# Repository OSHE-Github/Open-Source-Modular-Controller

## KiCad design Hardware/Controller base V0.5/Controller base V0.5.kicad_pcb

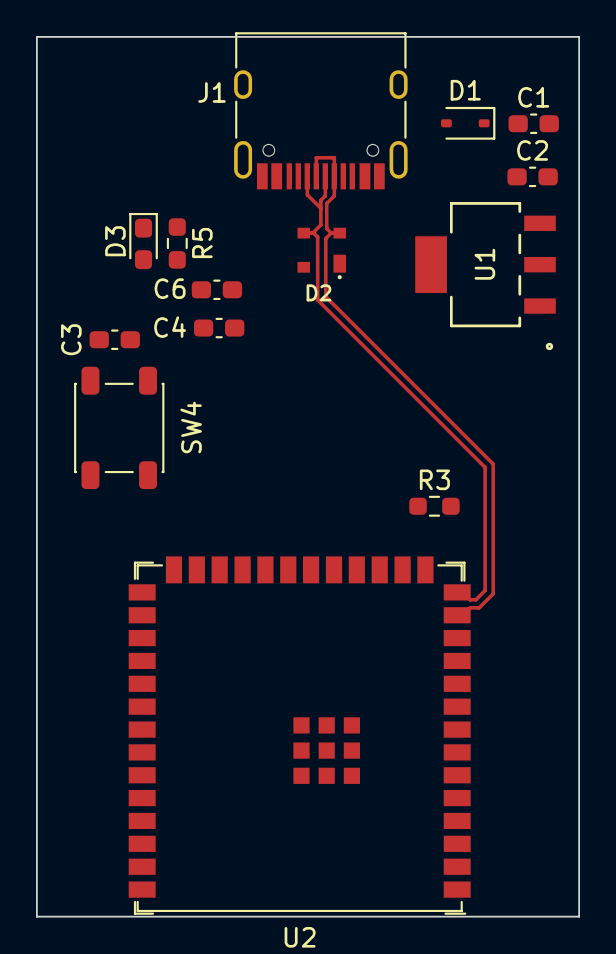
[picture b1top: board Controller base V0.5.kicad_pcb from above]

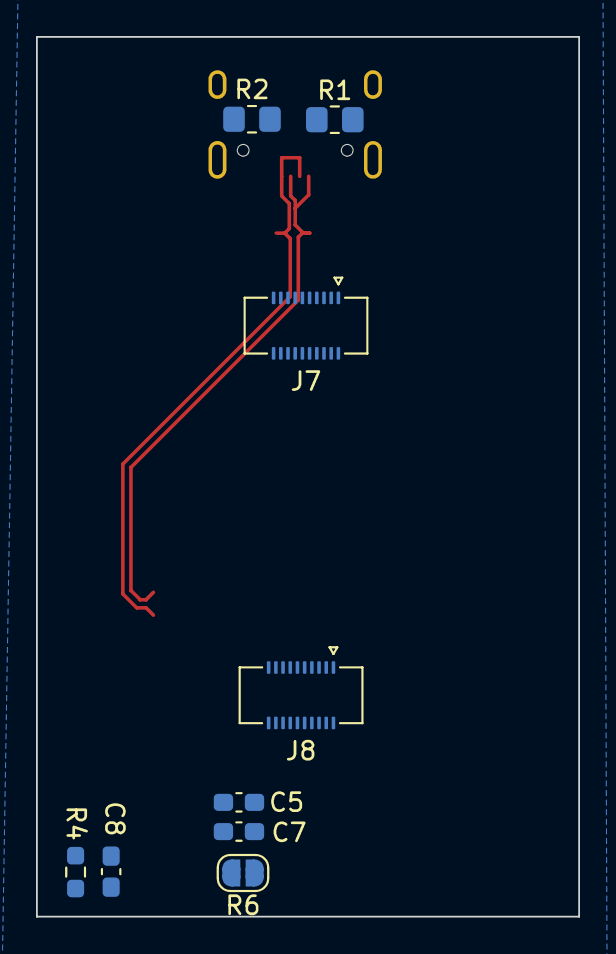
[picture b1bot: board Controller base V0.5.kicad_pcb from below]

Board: 2 copper layers, 30.1 x 48.9 mm, 23 parts (9 on the bottom side), 41 nets.

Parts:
C1, C5, C6: 10uF; C_0603_1608Metric_Pad1.08x0.95mm_HandSolder
C2, C3, C4, C7: 0.1uF; C_0603_1608Metric_Pad1.08x0.95mm_HandSolder
C8: 1uF; C_0603_1608Metric_Pad1.08x0.95mm_HandSolder
D1: 1N5819WS; D_SOD-323
D2: PRTR5V0U2X_215
D3: LED; LED_0603_1608Metric_Pad1.05x0.95mm_HandSolder
J1: USB_C_Receptacle_USB2.0_16P; USB_C_Receptacle_HRO_TYPE-C-31-M-12
J7, J8: Conn_02x10_Counter_Clockwise; Hirose_DF40C-20DS-0.4V_2x10_P0.4mm
R1, R2: 5.1K; R_0805_2012Metric_Pad1.20x1.40mm_HandSolder
R3, R5: 1K; R_0603_1608Metric_Pad0.98x0.95mm_HandSolder
R4: 10K; R_0603_1608Metric_Pad0.98x0.95mm_HandSolder
R6: 0; SolderJumper-2_P1.3mm_Open_RoundedPad1.0x1.5mm
SW4: SW_Push; SW_SPST_PTS647_Sx38
U1: AZ1117CH-3.3TRG1; SOT-223_DIO
U2: ESP32-S3-WROOM-1U-N4; ESP32-S3-WROOM-1U

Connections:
/CC1: J1.A5 (CC1), R2.2
/CC2: J1.B5 (CC2), R1.2
/CHIP_PU: C8.1, R4.1, U2.3 (EN)
D+: D2.3, J1.A6 (D+), J1.B6 (D+), U2.14 (USB_D+)
D-: D2.2, J1.A7 (D-), J1.B7 (D-), U2.13 (USB_D-)
ESP_3.3V: R4.2, R6.2, U2.2 (3V3)
GND: C1.2, C2.2, C3.1, C4.2, C5.2, C6.2, C7.2, C8.2, D2.1, D3.1 (K), J1.A1 (GND), J1.A12 (GND), J1.B1 (GND), J1.B12 (GND), J1.S1 (SHIELD), J7.11, J7.13, J7.15, J8.15, J8.17, J8.19, R1.1, R2.1, SW4.1, U1.1 (GND), U2.1 (GND), U2.40 (GND), U2.41 (GND)
GPIO0: C3.2, SW4.2, U2.27 (IO0)
GPIO1: J8.12, U2.39 (IO1)
GPIO2: J8.10, U2.38 (IO2)
GPIO3: J7.16, R3.1, U2.15 (IO3)
GPIO4: J8.14, U2.4 (IO4)
GPIO5: J8.16, U2.5 (IO5)
GPIO6: J8.18, U2.6 (IO6)
GPIO7: J8.20, U2.7 (IO7)
GPIO8: J7.18, U2.12 (IO8)
GPIO9: J7.14, U2.17 (IO9)
GPIO10: J7.12, U2.18 (IO10)
GPIO11: J7.10, U2.19 (IO11)
GPIO12: J7.8, U2.20 (IO12)
GPIO13: J7.6, U2.21 (IO13)
GPIO14: J7.4, U2.22 (IO14)
GPIO15: J8.9, U2.8 (IO15)
GPIO16: J8.11, U2.9 (IO16)
GPIO17: J8.13, U2.10 (IO17)
GPIO18: J7.20, U2.11 (IO18)
GPIO21: J7.2, U2.23 (IO21)
GPIO35: J8.1, U2.28 (IO35)
GPIO36: J8.3, U2.29 (IO36)
GPIO37: J8.5, U2.30 (IO37)
GPIO38: J8.7, U2.31 (IO38)
GPIO41: J8.2, U2.34 (IO41)
GPIO42: J8.4, U2.35 (IO42)
GPIO47: J7.3, U2.24 (IO47)
GPIO48: J7.1, U2.25 (IO48)
unnamed: D3.2 (A), R5.2
RXD0: J8.6, U2.36 (RXD0)
TXD0: J8.8, U2.37 (TXD0)
VBUS: D1.2 (A), D2.4, J1.A4 (VBUS), J1.A9 (VBUS), J1.B4 (VBUS), J1.B9 (VBUS)
VCC_3V3: C4.1, C5.1, C6.1, C7.1, J7.5, J7.7, J7.9, R3.2, R5.1, R6.1, U1.2 (OUTPUT)
VCC_5V: C1.1, C2.1, D1.1 (K), J7.17, J7.19, U1.3 (INPUT)

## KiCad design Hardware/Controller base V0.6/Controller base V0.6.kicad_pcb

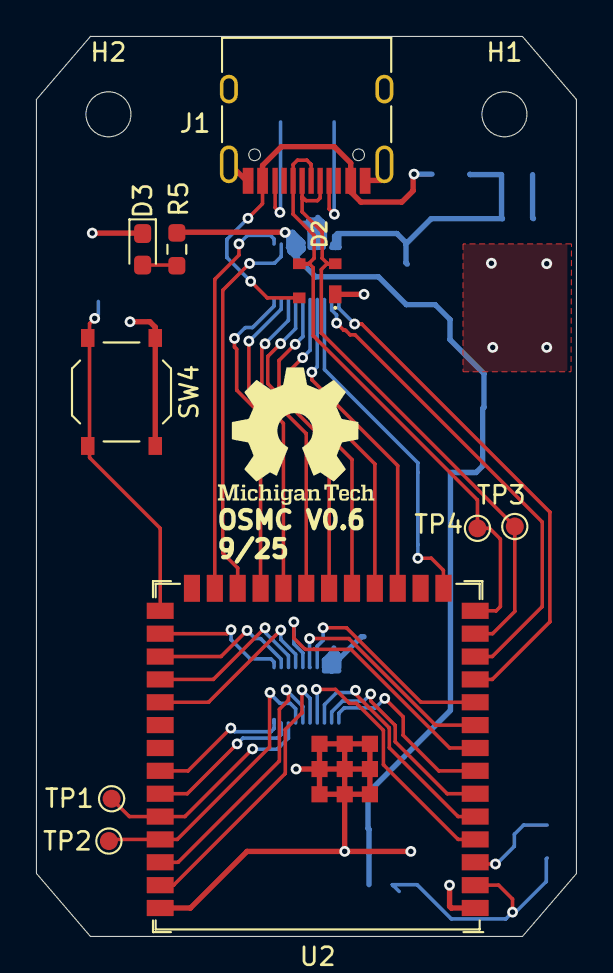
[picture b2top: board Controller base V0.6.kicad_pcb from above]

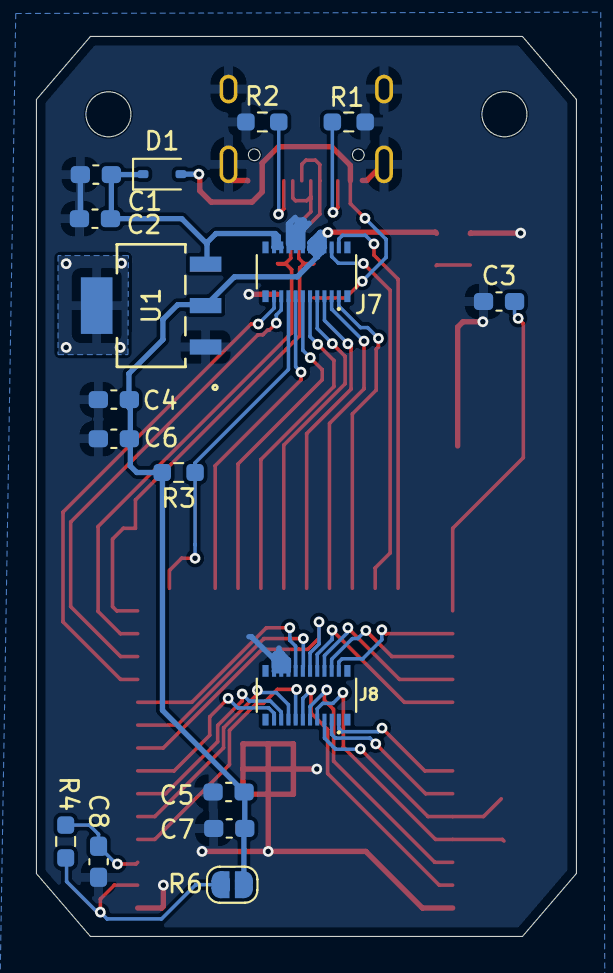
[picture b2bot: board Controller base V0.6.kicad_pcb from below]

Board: 2 copper layers, 30.0 x 50.0 mm, 29 parts (17 on the bottom side), 41 nets.

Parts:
C1, C5, C6: 10uF; C_0603_1608Metric_Pad1.08x0.95mm_HandSolder
C2, C3, C4, C7: 0.1uF; C_0603_1608Metric_Pad1.08x0.95mm_HandSolder
C8: 1uF; C_0603_1608Metric_Pad1.08x0.95mm_HandSolder
D1: 1N5819WS; D_SOD-323
D2: PRTR5V0U2X_215
D3: LED; LED_0603_1608Metric_Pad1.05x0.95mm_HandSolder
H1, H2: MountingHole; MountingHole_2.5mm
J1: USB_C_Receptacle_USB2.0_16P; USB_C_Receptacle_HRO_TYPE-C-31-M-12
J7, J8: Conn_02x10_Counter_Clockwise; HRS_DF40C-20DP-0.4V_51_
R1, R2: 5.1K; R_0603_1608Metric_Pad0.98x0.95mm_HandSolder
R3, R5: 1K; R_0603_1608Metric_Pad0.98x0.95mm_HandSolder
R4: 10K; R_0603_1608Metric_Pad0.98x0.95mm_HandSolder
R6: 0; SolderJumper-2_P1.3mm_Open_RoundedPad1.0x1.5mm
SW4: SW_Push; SW_Push_1P1T_XKB_TS-1187A
TP1, TP2, TP3, TP4: TestPoint; TestPoint_Pad_D1.0mm
U1: AZ1117CH-3.3TRG1; SOT-223_DIO
U2: ESP32-S3-WROOM-1U-N4; ESP32-S3-WROOM-1U

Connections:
/CC1: J1.A5 (CC1), R2.2
/CC2: J1.B5 (CC2), R1.2
/CHIP_PU: C8.1, R4.1, U2.3 (EN)
D+: D2.3, J1.A6 (D+), J1.B6 (D+), TP4.1, U2.14 (USB_D+)
D-: D2.2, J1.A7 (D-), J1.B7 (D-), TP3.1, U2.13 (USB_D-)
ESP_3.3V: R4.2, R6.2, U2.2 (3V3)
GND: C1.2, C2.2, C3.1, C4.2, C5.2, C6.2, C7.2, C8.2, D2.1, D3.1 (K), J1.A1 (GND), J1.A12 (GND), J1.B1 (GND), J1.B12 (GND), J1.S1 (SHIELD), J7.12, J7.14, J7.16, J8.16, J8.18, J8.20, R1.1, R2.1, SW4.1, U1.1 (GND), U2.1 (GND), U2.40 (GND), U2.41 (GND)
GPIO0: C3.2, SW4.2, U2.27 (IO0)
GPIO1: J8.11, U2.39 (IO1)
GPIO2: J8.9, U2.38 (IO2)
GPIO3: J7.15, R3.1, U2.15 (IO3)
GPIO4: J8.13, U2.4 (IO4)
GPIO5: J8.15, U2.5 (IO5)
GPIO6: J8.17, U2.6 (IO6)
GPIO7: J8.19, U2.7 (IO7)
GPIO8: J7.17, U2.12 (IO8)
GPIO9: J7.13, U2.17 (IO9)
GPIO10: J7.11, U2.18 (IO10)
GPIO11: J7.9, U2.19 (IO11)
GPIO12: J7.7, U2.20 (IO12)
GPIO13: J7.5, U2.21 (IO13)
GPIO14: J7.3, U2.22 (IO14)
GPIO15: J8.10, U2.8 (IO15)
GPIO16: J8.12, U2.9 (IO16)
GPIO17: J8.14, U2.10 (IO17)
GPIO18: J7.19, U2.11 (IO18)
GPIO21: J7.1, U2.23 (IO21)
GPIO35: J8.2, U2.28 (IO35)
GPIO36: J8.4, U2.29 (IO36)
GPIO37: J8.6, U2.30 (IO37)
GPIO38: J8.8, U2.31 (IO38)
GPIO41: J8.1, U2.34 (IO41)
GPIO42: J8.3, U2.35 (IO42)
GPIO47: J7.4, U2.24 (IO47)
GPIO48: J7.2, U2.25 (IO48)
unnamed: D3.2 (A), R5.2
RXD0: J8.5, TP1.1, U2.36 (RXD0)
TXD0: J8.7, TP2.1, U2.37 (TXD0)
VBUS: D1.2 (A), D2.4, J1.A4 (VBUS), J1.A9 (VBUS), J1.B4 (VBUS), J1.B9 (VBUS)
VCC_3V3: C4.1, C5.1, C6.1, C7.1, J7.6, J7.8, J7.10, R3.2, R5.1, R6.1, U1.2 (OUTPUT)
VCC_5V: C1.1, C2.1, D1.1 (K), J7.18, J7.20, U1.3 (INPUT)

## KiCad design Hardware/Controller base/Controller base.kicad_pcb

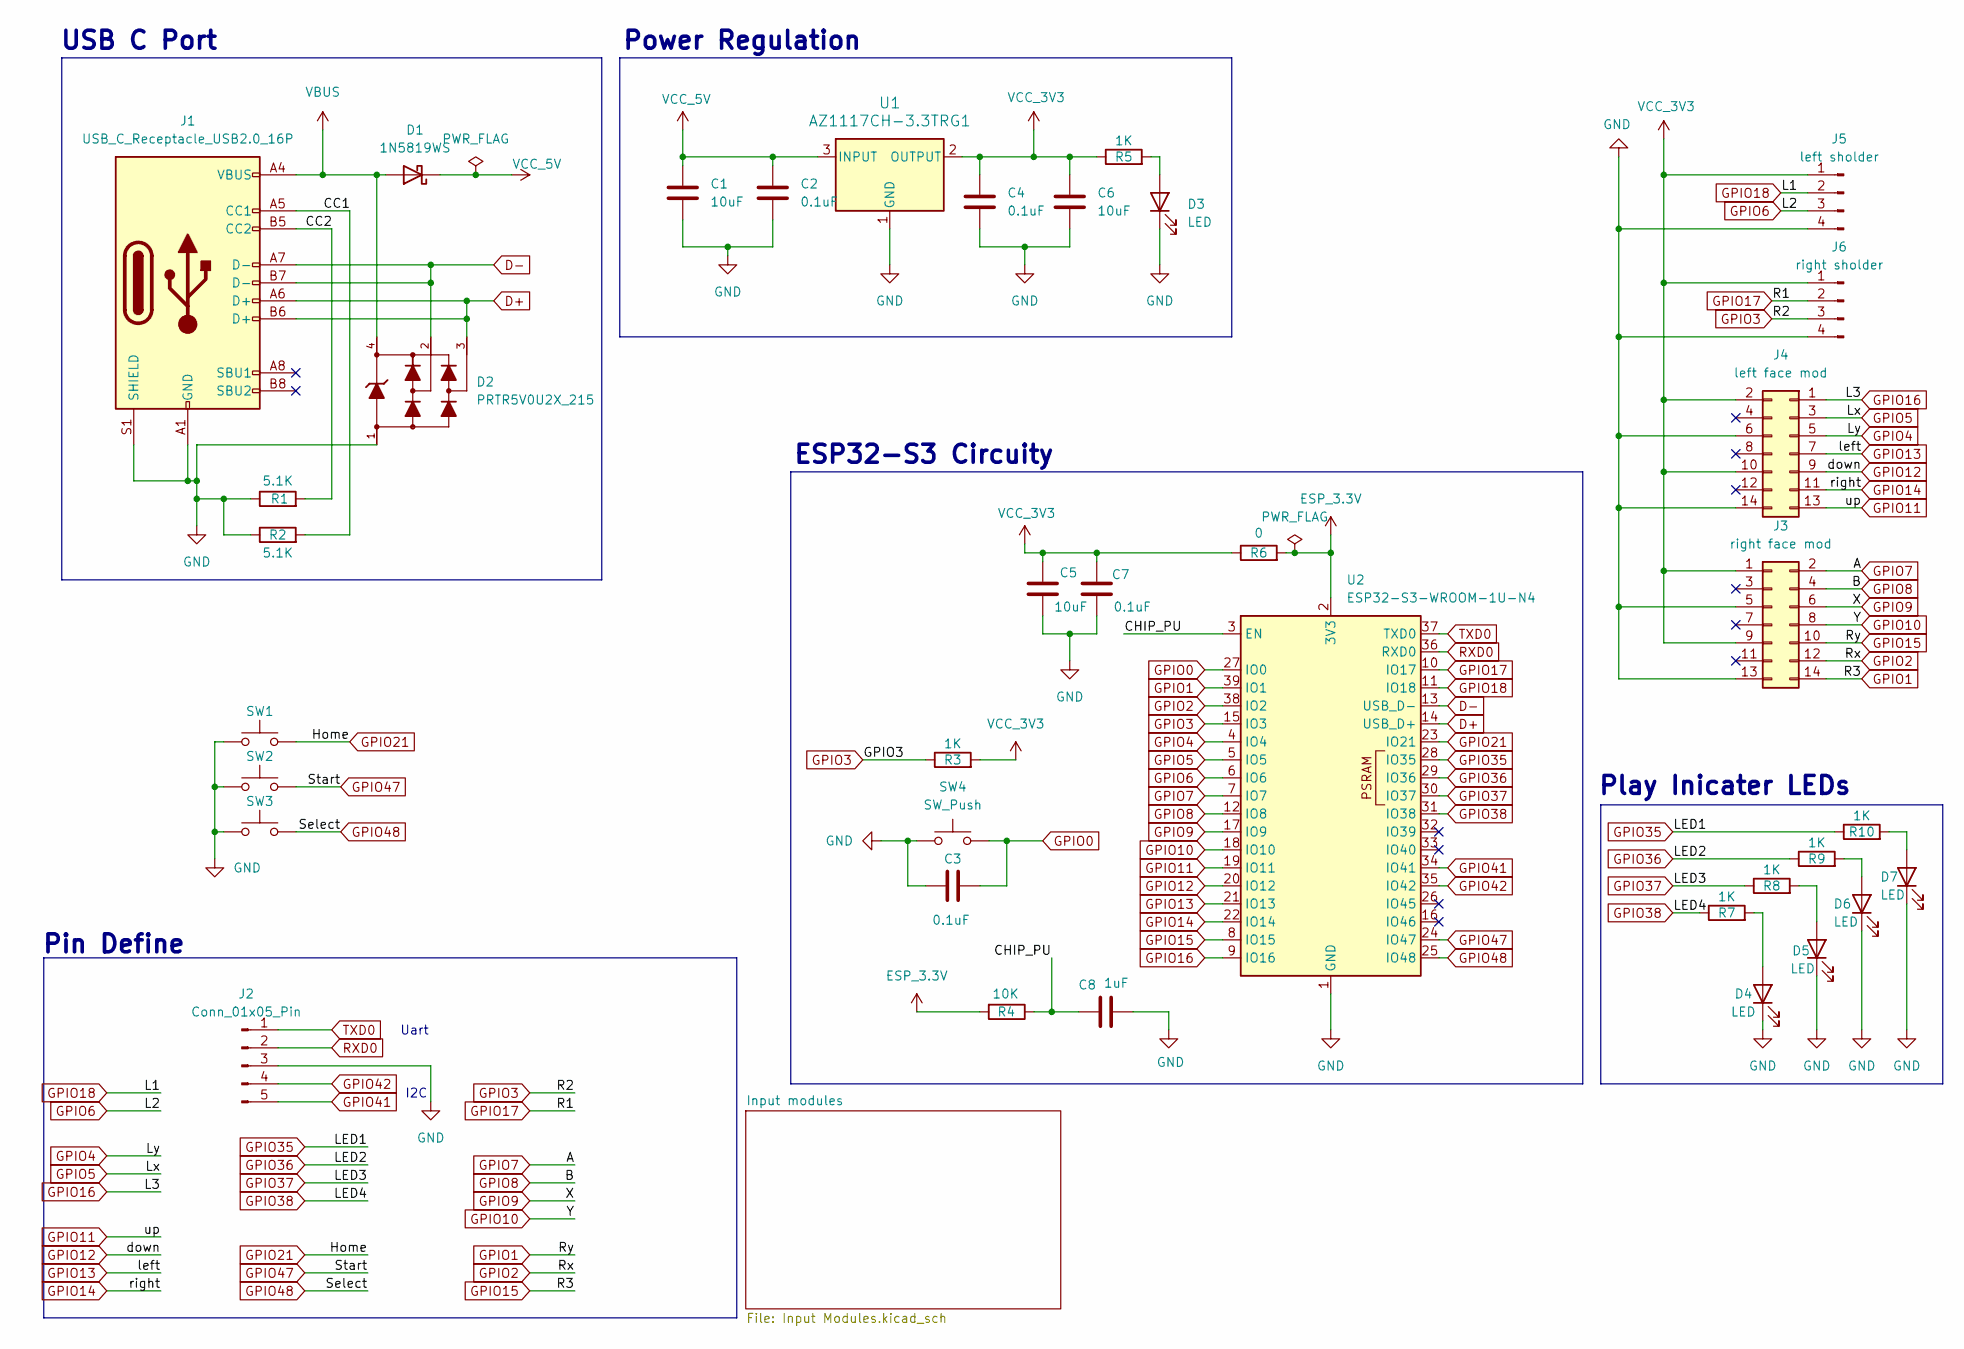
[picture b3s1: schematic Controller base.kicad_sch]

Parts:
C1, C5, C6: 10uF; C_0805_2012Metric_Pad1.18x1.45mm_HandSolder
C2, C3, C4, C7: 0.1uF; C_0805_2012Metric_Pad1.18x1.45mm_HandSolder
C8: 1uF; C_0805_2012Metric_Pad1.18x1.45mm_HandSolder
D1: 1N5819WS; D_SOD-323
D2: PRTR5V0U2X_215
D3, D4, D5, D6, D7: LED; LED_0603_1608Metric_Pad1.05x0.95mm_HandSolder
J1: USB_C_Receptacle_USB2.0_16P; USB_C_Receptacle_HRO_TYPE-C-31-M-12
J2: Conn_01x05_Pin; JST_EH_S5B-EH_1x05_P2.50mm_Horizontal
J3: right face mod; PinHeader_2x07_P1.27mm_Vertical
J4: left face mod; PinHeader_2x07_P1.27mm_Vertical
J5: left sholder; PinHeader_1x04_P1.27mm_Vertical
J6: right sholder; PinHeader_1x04_P1.27mm_Vertical
R1, R2: 5.1K; R_0805_2012Metric_Pad1.20x1.40mm_HandSolder
R3, R5, R7, R8, R9, R10: 1K; R_0603_1608Metric_Pad0.98x0.95mm_HandSolder
R4: 10K; R_0603_1608Metric_Pad0.98x0.95mm_HandSolder
R6: 0; SolderJumper-2_P1.3mm_Open_RoundedPad1.0x1.5mm
SW1, SW2, SW3: SW_Push; SW_Push_1P1T_XKB_TS-1187A
SW4: SW_Push; SW_SPST_PTS647_Sx38
U1: AZ1117CH-3.3TRG1; SOT-223_DIO
U2: ESP32-S3-WROOM-1U-N4; ESP32-S3-WROOM-1U

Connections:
/CC1: J1.A5 (CC1), R2.2
/CC2: J1.B5 (CC2), R1.2
/CHIP_PU: C8.1, R4.1, U2.3 (EN)
D+: D2.3, J1.A6 (D+), J1.B6 (D+), U2.14 (USB_D+)
D-: D2.2, J1.A7 (D-), J1.B7 (D-), U2.13 (USB_D-)
ESP_3.3V: R4.2, R6.2, U2.2 (3V3)
GND: C1.2, C2.2, C3.1, C4.2, C5.2, C6.2, C7.2, C8.2, D2.1, D3.1 (K), D4.1 (K), D5.1 (K), D6.1 (K), D7.1 (K), J1.A1 (GND), J1.A12 (GND), J1.B1 (GND), J1.B12 (GND), J1.S1 (SHIELD), J2.3, J3.5, J3.13, J4.6, J4.14, J5.4, J6.4, R1.1, R2.1, SW1.1, SW2.1, SW3.1, SW4.1, U1.1 (GND), U2.1 (GND), U2.40 (GND), U2.41 (GND)
GPIO0: C3.2, SW4.2, U2.27 (IO0)
GPIO1: J3.10, J3.14, U2.8 (IO15), U2.39 (IO1)
GPIO2: J3.12, U2.38 (IO2)
GPIO3: J6.3, R3.1, U2.15 (IO3)
GPIO4: J4.5, U2.4 (IO4)
GPIO5: J4.3, U2.5 (IO5)
GPIO6: J5.3, U2.6 (IO6)
GPIO7: J3.2, U2.7 (IO7)
GPIO8: J3.4, U2.12 (IO8)
GPIO9: J3.6, U2.17 (IO9)
GPIO10: J3.8, U2.18 (IO10)
GPIO11: J4.13, U2.19 (IO11)
GPIO12: J4.9, U2.20 (IO12)
GPIO13: J4.7, U2.21 (IO13)
GPIO14: J4.11, U2.22 (IO14)
GPIO16: J4.1, U2.9 (IO16)
GPIO17: J6.2, U2.10 (IO17)
GPIO18: J5.2, U2.11 (IO18)
GPIO21: SW1.2, U2.23 (IO21)
GPIO35: R10.1, U2.28 (IO35)
GPIO36: R9.1, U2.29 (IO36)
GPIO37: R8.1, U2.30 (IO37)
GPIO38: R7.1, U2.31 (IO38)
GPIO41: J2.5, U2.34 (IO41)
GPIO42: J2.4, U2.35 (IO42)
GPIO47: SW2.2, U2.24 (IO47)
GPIO48: SW3.2, U2.25 (IO48)
unnamed: D3.2 (A), R5.2
unnamed: D4.2 (A), R7.2
unnamed: D5.2 (A), R8.2
unnamed: D6.2 (A), R9.2
unnamed: D7.2 (A), R10.2
RXD0: J2.2, U2.36 (RXD0)
TXD0: J2.1, U2.37 (TXD0)
VBUS: D1.2 (A), D2.4, J1.A4 (VBUS), J1.A9 (VBUS), J1.B4 (VBUS), J1.B9 (VBUS)
VCC_3V3: C4.1, C5.1, C6.1, C7.1, J3.1, J3.9, J4.2, J4.10, J5.1, J6.1, R3.2, R5.1, R6.1, U1.2 (OUTPUT)
VCC_5V: C1.1, C2.1, D1.1 (K), U1.3 (INPUT)

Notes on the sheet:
ESP32-S3 Circuity
Uart
USB C Port
Play Inicater LEDs
I2C
Power Regulation
Pin Define

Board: 2 copper layers, 35 parts (15 on the bottom side), 44 nets, no tracks yet.

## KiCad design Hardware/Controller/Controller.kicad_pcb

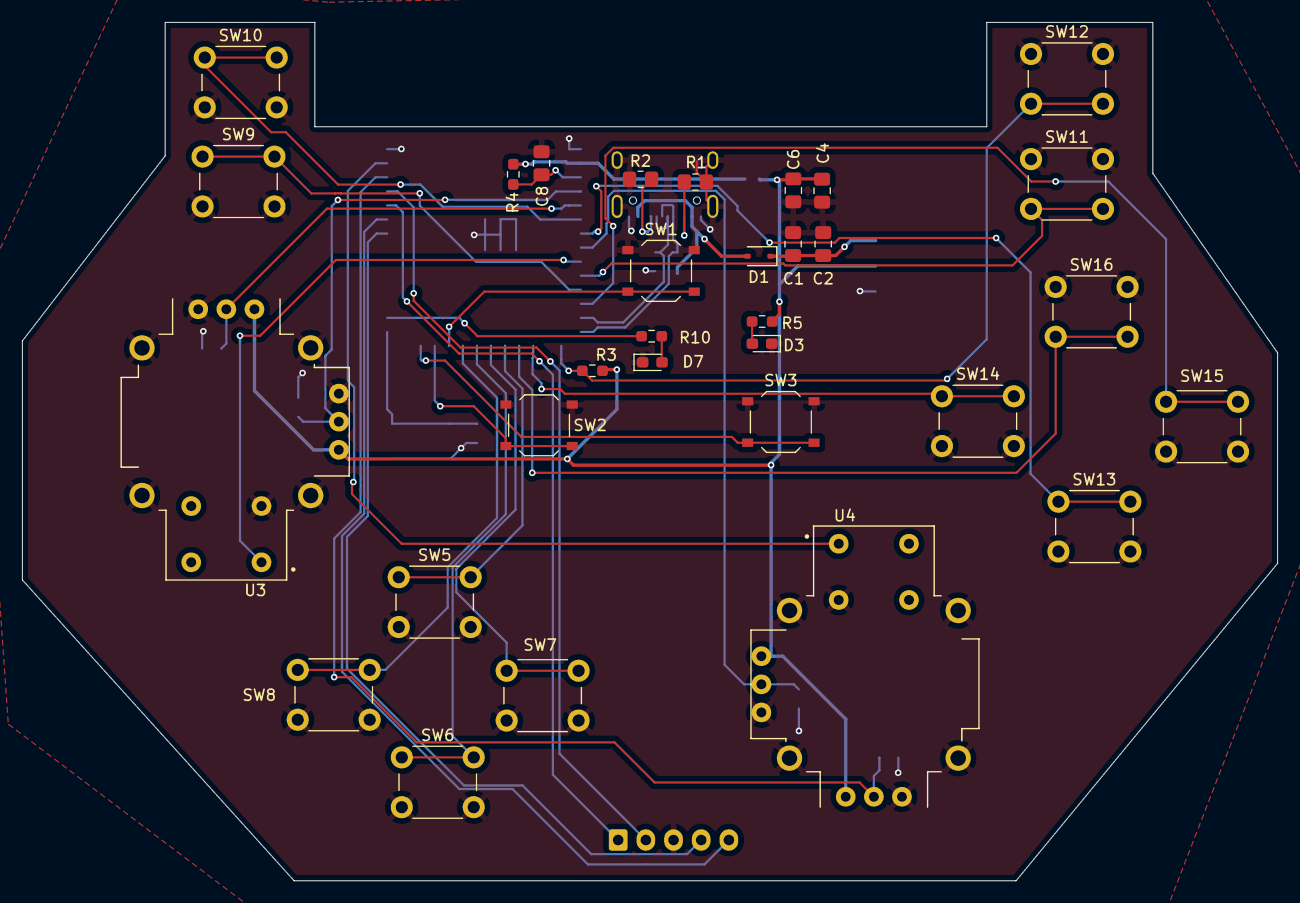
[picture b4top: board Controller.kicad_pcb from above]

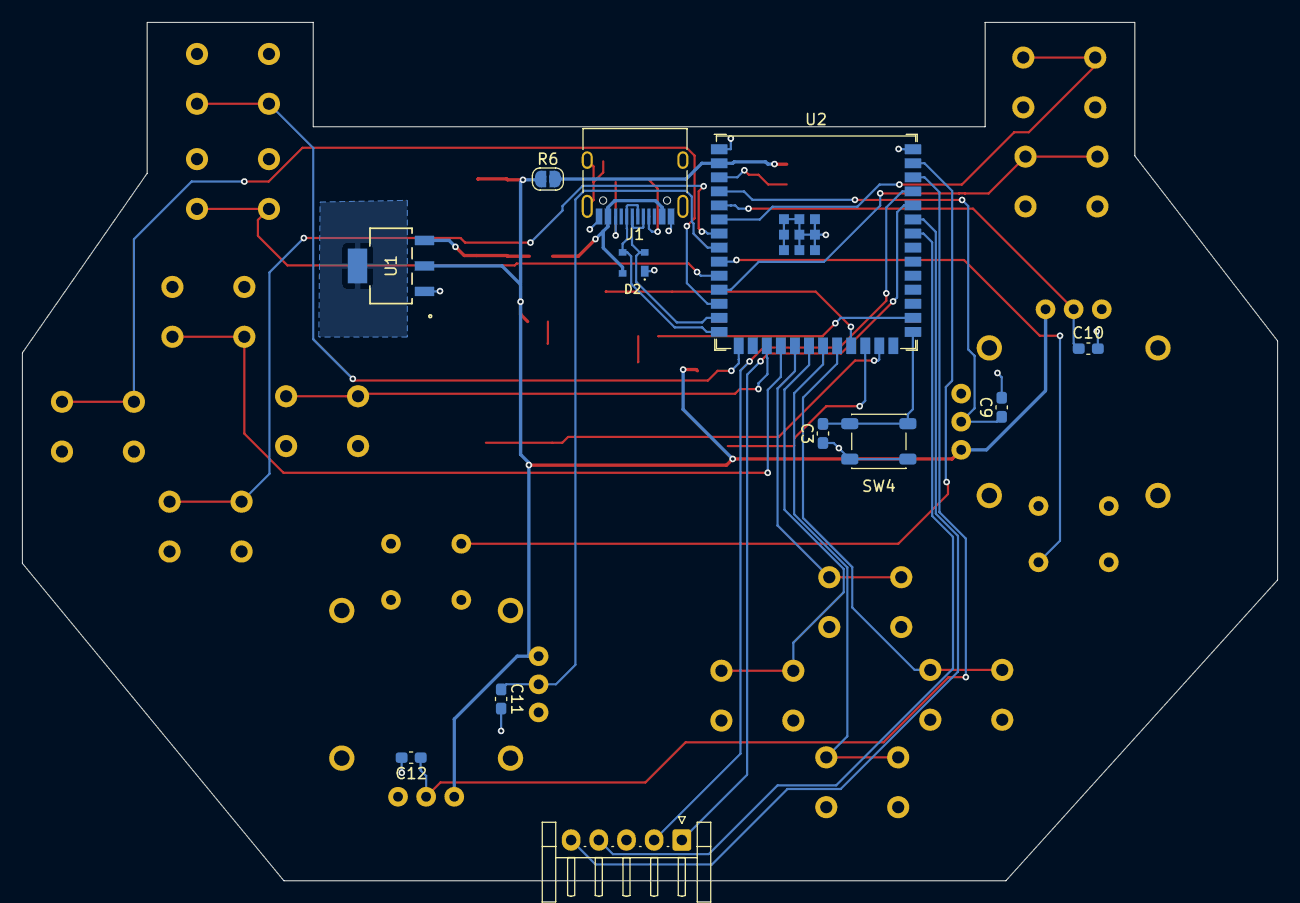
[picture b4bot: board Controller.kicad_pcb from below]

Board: 2 copper layers, 113.4 x 77.6 mm, 43 parts (12 on the bottom side), 39 nets.

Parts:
C1, C6: 10uF; C_0805_2012Metric_Pad1.18x1.45mm_HandSolder
C2, C4: 0.1uF; C_0805_2012Metric_Pad1.18x1.45mm_HandSolder
C3: 0.1uF; C_0603_1608Metric_Pad1.08x0.95mm_HandSolder
C8: 1uF; C_0805_2012Metric_Pad1.18x1.45mm_HandSolder
C9, C10, C11, C12: 1uF; C_0603_1608Metric_Pad1.08x0.95mm_HandSolder
D1: 1N5819WS; D_SOD-323
D2: PRTR5V0U2X_215
D3, D7: LED; LED_0603_1608Metric_Pad1.05x0.95mm_HandSolder
J1: USB_C_Receptacle_USB2.0_16P; USB_C_Receptacle_HRO_TYPE-C-31-M-12
J2: Conn_01x05_Pin; JST_EH_S5B-EH_1x05_P2.50mm_Horizontal
R1, R2: 5.1K; R_0805_2012Metric_Pad1.20x1.40mm_HandSolder
R3, R5, R10: 1K; R_0603_1608Metric_Pad0.98x0.95mm_HandSolder
R4: 10K; R_0603_1608Metric_Pad0.98x0.95mm_HandSolder
R6: 0; SolderJumper-2_P1.3mm_Open_RoundedPad1.0x1.5mm
SW1, SW2, SW3: SW_Push; SW_Push_1P1T_XKB_TS-1187A
SW4: SW_Push; SW_SPST_PTS647_Sx38
SW5, SW6, SW7, SW8, SW9, SW10, SW11, SW12, SW13, SW14, SW15, SW16: SW_Push; SW_PUSH_6mm
U1: AZ1117CH-3.3TRG1; SOT-223_DIO
U2: ESP32-S3-WROOM-1U-N4; ESP32-S3-WROOM-1U
U3, U4: COM-09032; XDCR_COM-09032

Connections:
/CC1: J1.A5 (CC1), R2.2
/CC2: J1.B5 (CC2), R1.2
/CHIP_PU: C8.1, R4.1, U2.3 (EN)
D+: D2.3, J1.A6 (D+), J1.B6 (D+), U2.14 (USB_D+)
D-: D2.2, J1.A7 (D-), J1.B7 (D-), U2.13 (USB_D-)
ESP_3.3V: R4.2, R6.2, U2.2 (3V3)
GND: C1.2, C2.2, C3.1, C4.2, C6.2, C8.2, C9.2, C10.2, C11.2, C12.2, D2.1, D3.1 (K), D7.1 (K), J1.A1 (GND), J1.A12 (GND), J1.B1 (GND), J1.B12 (GND), J1.S1 (SHIELD), J2.3, R1.1, R2.1, SW1.1, SW2.1, SW3.1, SW4.1, SW5.2, SW6.2, SW7.1, SW8.1, SW9.2, SW10.2, SW11.1, SW12.1, SW13.2, SW14.2, SW15.1, SW16.1, U1.1 (GND), U2.1 (GND), U2.40 (GND), U2.41 (GND), U3.B2A (SEL-), U3.H3 (H-), U3.S1 (SHIELD), U3.S2 (SHIELD__1), U3.S3 (SHIELD__2), U3.S4 (SHIELD__3), U3.V3 (V-), U4.B2A (SEL-), U4.H3 (H-), U4.S1 (SHIELD), U4.S2 (SHIELD__1), U4.S3 (SHIELD__2), U4.S4 (SHIELD__3), U4.V3 (V-)
GPIO0: C3.2, SW4.2, U2.27 (IO0)
GPIO1: U2.39 (IO1), U4.B1A (SEL+)
GPIO2: C12.1, U2.38 (IO2), U4.H2 (H)
GPIO3: R3.1, SW12.2, U2.15 (IO3)
GPIO4: C9.1, U2.4 (IO4), U3.V2 (V)
GPIO5: C10.1, U2.5 (IO5), U3.H2 (H)
GPIO6: SW10.1, U2.6 (IO6)
GPIO7: SW13.1, U2.7 (IO7)
GPIO8: SW15.2, U2.12 (IO8)
GPIO9: SW14.1, U2.17 (IO9)
GPIO10: SW16.2, U2.18 (IO10)
GPIO11: SW5.1, U2.19 (IO11)
GPIO12: SW7.2, U2.20 (IO12)
GPIO13: SW6.1, U2.21 (IO13)
GPIO14: SW8.2, U2.22 (IO14)
GPIO15: C11.1, U2.8 (IO15), U4.V2 (V)
GPIO16: U2.9 (IO16), U3.B1A (SEL+)
GPIO17: SW11.2, U2.10 (IO17)
GPIO18: SW9.1, U2.11 (IO18)
GPIO21: SW1.2, U2.23 (IO21)
GPIO35: R10.1, U2.28 (IO35)
GPIO41: J2.4, U2.34 (IO41)
GPIO42: J2.5, U2.35 (IO42)
GPIO47: SW2.2, U2.24 (IO47)
GPIO48: SW3.2, U2.25 (IO48)
unnamed: D3.2 (A), R5.2
unnamed: D7.2 (A), R10.2
RXD0: J2.1, U2.36 (RXD0)
TXD0: J2.2, U2.37 (TXD0)
VBUS: D1.2 (A), D2.4, J1.A4 (VBUS), J1.A9 (VBUS), J1.B4 (VBUS), J1.B9 (VBUS)
VCC_3V3: C4.1, C6.1, R3.2, R5.1, R6.1, U1.2 (OUTPUT), U3.H1 (H+), U3.V1 (V+), U4.H1 (H+), U4.V1 (V+)
VCC_5V: C1.1, C2.1, D1.1 (K), U1.3 (INPUT)

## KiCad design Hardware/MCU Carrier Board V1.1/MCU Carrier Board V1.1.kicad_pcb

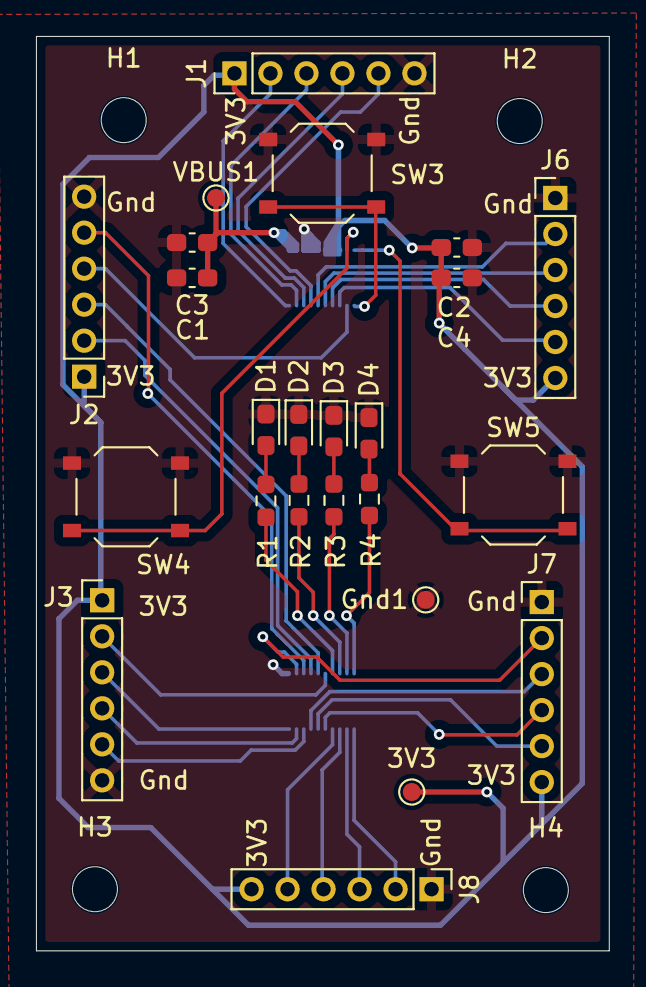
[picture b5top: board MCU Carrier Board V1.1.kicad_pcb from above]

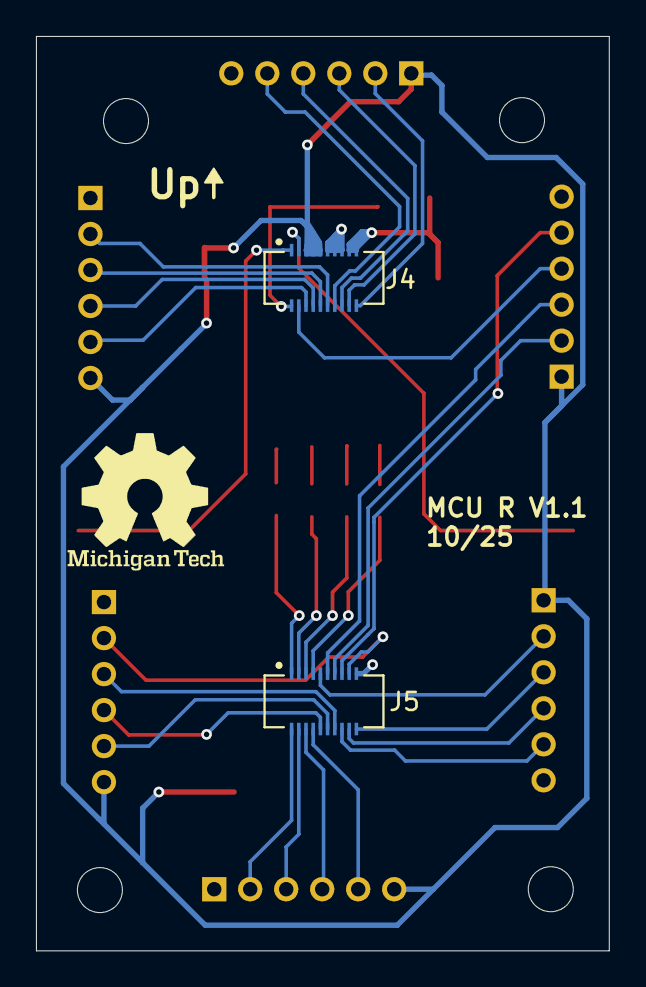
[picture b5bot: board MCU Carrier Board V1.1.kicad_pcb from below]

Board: 2 copper layers, 31.8 x 50.8 mm, 30 parts (2 on the bottom side), 38 nets.

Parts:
3V3: TestPoint; TestPoint_Pad_D1.0mm
C1, C2: .1uF; C_0603_1608Metric_Pad1.08x0.95mm_HandSolder
C3, C4: 10uF; C_0603_1608Metric_Pad1.08x0.95mm_HandSolder
D1, D2, D3, D4: LED; LED_0603_1608Metric_Pad1.05x0.95mm_HandSolder
Gnd1: TestPoint; TestPoint_Pad_D1.0mm
H1, H2, H3, H4: MountingHole; MountingHole_2.5mm
J1, J2, J3, J6, J7, J8: Conn_01x06_Pin; PinHeader_1x06_P2.00mm_Vertical
J4: Top Connector; HRS_DF40C-20DS-0.4V_51_
J5: Bottom Connector; HRS_DF40C-20DS-0.4V_51_
R1, R2, R3, R4: 1K; R_0603_1608Metric_Pad0.98x0.95mm_HandSolder
SW3, SW4, SW5: SW_Push; SW_Push_1P1T_XKB_TS-1187A
VBUS1: TestPoint; TestPoint_Pad_D1.0mm

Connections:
GND: C1.1, C2.2, C3.1, C4.2, D1.1 (K), D2.1 (K), D3.1 (K), D4.1 (K), Gnd1.1, J1.6, J2.6, J3.6, J4.11, J4.13, J4.15, J5.19, J6.1, J7.1, J8.1, SW3.1, SW4.1, SW5.1
GPIO1: J5.12, J7.5
GPIO2: J5.10, J7.4
GPIO3: J1.4, J4.16
GPIO4: J5.14, J7.3
GPIO5: J3.5, J5.16
GPIO6: J3.4, J5.18
GPIO7: J3.3, J5.20
GPIO8: J1.3, J4.18
GPIO9: J1.5, J4.14
GPIO10: J4.12, J6.2
GPIO11: J4.10, J6.3
GPIO12: J4.8, J6.4
GPIO13: J4.6, J6.5
GPIO14: J2.4, J4.4
GPIO15: J3.2, J5.9
GPIO16: J2.3, J5.11
GPIO17: J2.2, J5.13
GPIO18: J1.2, J4.20
GPIO21: J4.2, SW3.2
GPIO35: J5.1, R4.1
GPIO36: J5.3, R3.1
GPIO37: J5.5, R2.1
GPIO38: J5.7, R1.1
GPIO39: J2.5, J5.15
GPIO40: J5.17, J7.2
GPIO41: J5.2, J8.2
GPIO42: J5.4, J8.3
GPIO47: J4.3, SW4.2
GPIO48: J4.1, SW5.2
unnamed: D1.2 (A), R1.2
unnamed: D2.2 (A), R2.2
unnamed: D3.2 (A), R3.2
unnamed: D4.2 (A), R4.2
RXD0: J5.6, J8.4
TXD0: J5.8, J8.5
VCC_3V3: 3V3.1, C2.1, C4.1, J1.1, J2.1, J3.1, J4.5, J4.7, J4.9, J6.6, J7.6, J8.6
VCC_5V: C1.2, C3.2, J4.17, J4.19, VBUS1.1
